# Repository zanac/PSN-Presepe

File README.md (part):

# PSN-Presepe

## Demo online Wokwi

▶️ [Apri la simulazione interattiva PSN-Presepe su Wokwi](https://wokwi.com/projects/476035349322038273)

La demo permette di provare direttamente dal browser il ciclo giorno/notte, le strisce RGB, il cielo stellato, OLED e comandi senza hardware reale.

Controller basato su Arduino Mega 2560 per la gestione modulare di un presepe a 12 V.

**Italiano** | [English](README_EN.md)

## Mockup della centralina

> Mockup concettuale della disposizione della centralina. Per i collegamenti elettrici fare riferimento agli schemi vettoriali presenti nella cartella `docs/`.

## Schema elettrico

> Questo è lo **schema di riferimento aggiornato** per il cablaggio. La striscia RGB 12 V è a positivo comune: il +12 V è diretto, mentre R, G e B vengono commutati sul lato negativo dai MOSFET.

## Mappatura hardware attuale

I pin di Arduino **non alimentano direttamente i carichi a 12 V**. Ogni uscita del Mega pilota l'ingresso `PWM` del relativo canale MOSFET. I normali carichi a due fili possono utilizzare la coppia `OUT+` / `OUT-`; la striscia RGB a positivo comune viene invece collegata come indicato qui sotto.

### MOSFET #1 — Cielo RGB

| Arduino Mega | Ingresso MOSFET | Uscita MOSFET | Carico 12 V | Controllo |
|---:|---|---|---|---|
| D2 | PWM1 | OUT1- | Striscia RGB — ritorno R | PWM / dimmerabile |
| D3 | PWM2 | OUT2- | Striscia RGB — ritorno G | PWM / dimmerabile |
| D4 | PWM3 | OUT3- | Striscia RGB — ritorno B | PWM / dimmerabile |
| — | PWM4 | OUT4+ / OUT4- | **Libero** | — |

La striscia RGB è un carico **12 V a positivo comune (anodo comune)**. Il suo unico filo `+12 V` viene collegato direttamente alla distribuzione +12 V protetta/WAGO e rimane sempre alimentato. I tre canali MOSFET commutano invece i ritorni R/G/B sul lato negativo:

```text
+12 V alimentatore ──► F1 CIELO ──┬──► +12 V comune RGB
                                   └──► DC+ MOSFET #1

RGB R ─────────────────────────────────────────► OUT1-
RGB G ─────────────────────────────────────────► OUT2-
RGB B ─────────────────────────────────────────► OUT3-

Mega D2 ───────────────────────────────────────► PWM1  (Rosso)
Mega D3 ───────────────────────────────────────► PWM2  (Verde)
Mega D4 ───────────────────────────────────────► PWM3  (Blu)

0 V alimentatore ──────────────────────────────► DC- MOSFET
```

La striscia RGB **non deve essere cablata come tre carichi indipendenti a due fili**. In questa configurazione `OUT1+`, `OUT2+` e `OUT3+` non sono necessari per la striscia RGB.

### Stelle WS2811 indirizzabili

Le stelle sono ora una stringa **WS2811 12 V da 50 pixel individualmente indirizzabili**. Non passano dal MOSFET: D5 è il segnale DATA.

```text
+12 V alimentatore ──► fusibile/distribuzione ──► WS2811 +12 V
0 V alimentatore ───────────────────────────────► WS2811 GND
Arduino GND ───────────────────────────────────► stesso 0 V comune
Mega D5 ── resistenza 330–470 Ω ──────────────► WS2811 DATA / DIN
```

Con le WS2811 il **GND Arduino deve essere comune allo 0 V dell'alimentatore 12 V**, perché il segnale DATA necessita dello stesso riferimento elettrico. Il Mega continua comunque a essere alimentato a 5 V via USB: il +12 V non deve mai essere collegato ai pin 5 V o I/O di Arduino.

Il firmware può comandare ogni stella separatamente, con luminosità e colore differenti. Dei 50 pixel disponibili, a ogni ciclo vengono selezionate casualmente 20 stelle attive, che compaiono progressivamente durante il crepuscolo e si spengono durante l'alba. Il canale 4 del MOSFET #1 rimane libero.

### MOSFET #3 e #4 — RGB laterali alba/tramonto

Per rendere alba e tramonto più dinamici vengono aggiunte **due strisce RGB analogiche 12 V da 1 m**, indipendenti dalla striscia principale:

| Posizione | Effetto | Mega R/G/B | Modulo |
|---|---|---|---|
| Sinistra | Tramonto | D7 / D11 / D12 | MOSFET #3, CH1–CH3 |
| Destra | Alba | D44 / D45 / D46 | MOSFET #4, CH1–CH3 |

Ogni striscia ha un ramo +12 V protetto dedicato: **F2 ALBA** alimenta sia il +12 V comune della striscia ALBA sia il DC+ del MOSFET #4; **F3 TRAMONTO** alimenta sia il +12 V comune della striscia TRAMONTO sia il DC+ del MOSFET #3. I ritorni R/G/B vanno ai tre OUT- del relativo modulo MOSFET. Il quarto canale di ciascun modulo resta libero. **D8 è dedicato al DATA della seconda catena WS2811 CASETTE.**

Nel firmware le palette RGB sono tarate per ottenere transizioni calde e progressive. Durante il **TRAMONTO** la laterale sinistra parte tenue, raggiunge al 38% un picco arancio chiaro e poi perde gradualmente saturazione; nell'ultimo 18% usa valori R=G=B e si spegne in bianco neutro. Il CIELO parte dalla tonalità lasciata dal GIORNO (210/82/18), diventa progressivamente bianco tenue e si spegne con R=G=B esattamente al picco del TRAMONTO. Durante l'**ALBA** la laterale destra segue una curva analoga, con picco al 38% leggermente meno arancione; il CIELO resta spento fino a quel picco e da lì cresce dolcemente fino alla tonalità iniziale del GIORNO.

### Relè ON/OFF — 4 moduli, 16 uscite

Luci case, pompe, mulino e gli altri carichi che richiedono soltanto ON/OFF vengono gestiti dai **quattro moduli relè 12 V a 4 canali**. I MOSFET restano dedicati ai carichi che richiedono PWM/dimmer.

| Gruppo | Mega | Modulo / ingresso |
|---|---:|---|
| Grp_01_01–Grp_01_04 | D25–D28 | RELÈ #1 IN1–IN4 |
| Grp_02_01–Grp_02_04 | D29–D32 | RELÈ #2 IN1–IN4 |
| Grp_03_01–Grp_03_04 | D33–D36 | RELÈ #3 IN1–IN4 |
| Grp_04_01–Grp_04_04 | D37–D40 | RELÈ #4 IN1–IN4 |

Per ogni scheda: **+12 V di alimentazione del ramo relè → DC+**, **0 V comune → DC-**. Il ramo di alimentazione delle schede relè verrà protetto e dimensionato separatamente quando sarà definita la distribuzione definitiva dei carichi. I morsetti COM/NO/NC restano disponibili per i futuri carichi. Per un carico normalmente spento si useranno normalmente COM + NO; la protezione del carico comandato è distinta da quella che alimenta l'elettronica della scheda relè.

I jumper S1–S4 permettono di scegliere HIGH/LOW trigger. Il firmware gestisce già le 16 uscite nella modalità TEST; nel simulatore viene usata la logica HIGH=ON. Prima del collegamento definitivo dei moduli reali va verificata la posizione dei jumper e, se necessario, impostato `RELE_ACTIVE_LOW` nel firmware.

#### Schedulazione scenografica dei relè

Le accensioni e gli spegnimenti durante il ciclo sono definiti nel firmware dalla tabella `SCHEDULAZIONE_RELE[]`. Ogni evento contiene:

`{ NOME_FASE, NOME_RELE, ACCESO_SPENTO, PERCENTUALE_FASE }`

La percentuale è **relativa alla singola fase**, non all'intero ciclo. Per esempio:

```cpp
const EventoRele SCHEDULAZIONE_RELE[] = {
  { TRAMONTO, Grp_01_03, true,  30 },
  { NOTTE,    Grp_01_03, false, 50 }
};
```

Con questa configurazione `Grp_01_03` si accende al **30% della fase TRAMONTO**, resta acceso durante il resto del tramonto, il crepuscolo e la prima metà della notte, quindi si spegne al **50% della fase NOTTE**.

Lo stato dei relè viene ricostruito dalla posizione corrente del ciclo, quindi rimane coerente anche usando **AVANTI**, pausa/ripresa o modificando la durata con il potenziometro. All'inizio di un nuovo ciclo, prima che siano raggiunti nuovi eventi, i relè partono spenti. In futuro la scenografia ON/OFF può essere modificata semplicemente aggiungendo o cambiando le righe della tabella.

### Display OLED ELEGOO EL-SM-008

Display di stato OLED **0,96 pollici, 128×64, I²C**, alimentazione 3,3–5 V, indirizzo I²C a 7 bit **0x3C**.

| OLED | Arduino Mega 2560 |
|---|---|
| GND | GND |
| VCC | 5 V |
| SDA | D20 / SDA |
| SCL | D21 / SCL |

Il display è **opzionale**: il firmware deve continuare a funzionare normalmente anche se l'OLED non è collegato. All'avvio il software verifica la presenza del display all'indirizzo 0x3C; se non risponde, prosegue senza OLED.

Il firmware usa il display come interfaccia di stato:
- schermata normale: **fase corrente**, percentuale di avanzamento della singola fase, barra grafica, RUN/PAUSA e durata totale del ciclo;
- START/STOP: mette in pausa o riprende il ciclo; in **PAUSA** l'OLED mostra stabilmente fase, percentuale della fase e i valori RGB correnti delle tre strisce; alla ripresa mostra brevemente **RIPRESA**;
- AVANTI: popup **AVANTI** con la nuova fase;
- TEST: feedback **TEST**;
- variazione significativa del B10K: popup **VELOCITA** con la durata effettiva del ciclo in minuti.

I popup durano circa 1,8 secondi e poi il display torna automaticamente alla schermata della fase. L'aggiornamento normale dell'OLED è non bloccante; l'assenza del display non impedisce l'avvio del controllore.

> Nota: sul Mega 2560 l'I²C hardware usa **D20=SDA** e **D21=SCL**. Eventuali esempi che indicano D21/D22 si riferiscono ad altre piattaforme, ad esempio ESP32.

Quando il ciclo viene messo in **PAUSA**, l'OLED mostra stabilmente la fase e la percentuale raggiunta, insieme ai valori RGB correnti delle tre strisce:

- `C R,G,B` = cielo RGB principale;
- `T R,G,B` = RGB laterale TRAMONTO;
- `A R,G,B` = RGB laterale ALBA.

I valori sono quelli logici 0–255 inviati al PWM e permettono di fermare la scena su una tonalità interessante, trascriverla e riutilizzarla successivamente per la taratura dei colori.

### Comandi

| Arduino Mega | Dispositivo | Collegamento |
|---:|---|---|
| D22 | Pulsante START/STOP | D22 ↔ pulsante ↔ GND logica |
| D23 | Pulsante AVANTI | D23 ↔ pulsante ↔ GND logica |
| D24 | Pulsante TEST | D24 ↔ pulsante ↔ GND logica |
| A0 | Potenziometro B10K velocità ciclo | 5 V ↔ esterno, A0 ↔ cursore, GND ↔ esterno |

> **Prova senza potenziometro:** se il potenziometro B10K su A0 viene scollegato, non lasciare A0 flottante: la lettura analogica potrebbe assumere valori casuali e far variare la durata del ciclo. Per una prova stabile, collegare temporaneamente **A0 direttamente a GND**. Il firmware leggerà A0=0, corrispondente alla durata minima del ciclo di **1 minuto**.

I pulsanti utilizzano `INPUT_PULLUP`, quindi non richiedono una resistenza di pull-up esterna. Il GND logico di Arduino viene distribuito tramite WAGO agli ingressi `GND1...GND4` dei MOSFET e ai comandi.

## Sequenza di inizializzazione all'accensione

Prima di iniziare il normale ciclo scenografico, il firmware esegue un **autotest visivo di circa 21,625 secondi**, seguito dalla schermata **PRONTO** per 900 ms. I relè restano spenti e le uscite luminose vengono provate in sequenza:

1. **ALBA** — striscia RGB alba in bianco brillante per circa **4,325 s**;
2. **CIELO** — striscia RGB principale in bianco brillante per circa **4,325 s**;
3. **TRAMONTO** — striscia RGB tramonto in bianco brillante per circa **4,325 s**;
4. **STELLE** — tutti i 50 pixel WS2811 in bianco brillante per circa **4,325 s**;
5. **CASETTE** — seconda catena WS2811 su D8 in bianco brillante per circa **4,325 s**.

La melodia **Astro del ciel** è stata dilatata a circa **21,625 s** per mantenere sincronizzati i cinque passi dell'autotest, la progress bar OLED e la musica. Al termine tutte le uscite vengono spente, compare **PRONTO** per 900 ms e solo dopo viene azzerato il timer del ciclo: il tempo di boot **non fa parte** del ciclo scenografico.

Durante l'intera sequenza l'OLED mostra **Inizializzazione**, il nome dell'uscita in prova, la percentuale complessiva e una progress bar.

## Funzionamento scenografico

Il ciclo automatico usa tre velocità discrete selezionate dal potenziometro: **1, 3 o 5 minuti**. Le fasi non hanno una durata fissa in secondi: occupano una percentuale precisa del ciclo, quindi tutti i tempi scalano linearmente quando si cambia la durata totale.

| Fase | Posizione nel ciclo | Quota ciclo | Ciclo 1 min | Ciclo 3 min | Ciclo 5 min |
|---|---:|---:|---:|---:|---:|
| **GIORNO** | 0–40% | 40% | 24 s | 72 s | 120 s |
| **TRAMONTO** | 40–50% | 10% | 6 s | 18 s | 30 s |
| **CREPUSCOLO** | 50–55% | 5% | 3 s | 9 s | 15 s |
| **NOTTE** | 55–85% | 30% | 18 s | 54 s | 90 s |
| **ALBA** | 85–100% | 15% | 9 s | 27 s | 45 s |

Questa tabella è il riferimento temporale del firmware. Per una durata intermedia, il tempo di ogni fase è semplicemente la percentuale indicata della durata totale.

1. **GIORNO (0–40%)** — stelle e laterali spente. Il CIELO parte caldo (210/82/18), raggiunge progressivamente il bianco pieno al 33% della fase, torna alla tonalità calda entro il 66% e la mantiene fino al TRAMONTO.
2. **TRAMONTO (40–50%)** — la laterale sinistra parte tenue e raggiunge al **38% della fase** un picco arancio chiaro (155/92/16), poi cala perdendo saturazione; nell'ultimo **18%** R=G=B e i tre canali si spengono insieme. Il CIELO parte dalla tonalità finale del GIORNO, si attenua verso un bianco tenue e raggiunge 0/0/0 esattamente al **38%**, cioè al picco della laterale, restando poi spento. Le stelle restano spente.
3. **CREPUSCOLO (50–55%)** — CIELO e laterali sono spenti. Viene generata una nuova disposizione casuale e compaiono progressivamente, una alla volta, **20 stelle scelte tra i 50 pixel disponibili**.
4. **NOTTE (55–85%)** — CIELO e laterali restano completamente spenti. Le 20 stelle rimangono attive con luminosità massime differenti e cicli asincroni individuali di variazione. Il ciclo individuale di ciascuna stella dura circa **6,4–12,2 s**, senza modificare la durata della fase NOTTE.
5. **ALBA (85–100%)** — le stelle iniziano a dissolversi fin dall'inizio. La laterale destra parte con pochissima luce chiara, raggiunge al **38% della fase** un picco arancio chiaro (155/78/22), poi cala perdendo saturazione; nell'ultimo **18%** R=G=B e si spegne in modo simultaneo. Il CIELO resta completamente spento fino al picco dell'ALBA; dal **38%** parte a luminosità molto bassa (10/4/1) e cresce dolcemente fino a 210/82/18, esattamente la tonalità con cui inizia il nuovo GIORNO.

La seconda catena WS2811 **CASETTE su D8** viene inizializzata dal firmware e verificata durante boot e TEST manuale, ma nel normale ciclo scenografico viene mantenuta spenta finché non saranno definite le sue accensioni.

A ogni nuovo CREPUSCOLO viene generata una nuova selezione delle stelle e delle relative luminosità. Il colore delle stelle è **bianco caldo**.

## Manuale di montaggio filo per filo

Questa sezione è il riferimento pratico per il cablaggio. **Non lavorare mai sul circuito con l'alimentatore 230 V collegato.** **Il +12 V non deve mai essere collegato direttamente a un pin del Mega, a 5 V, A0, SDA/SCL o DATA:** il Mega lavora a logica 5 V e i pin I/O non sono ingressi a 12 V. Il Mega è alimentato separatamente via USB 5 V. Il +12 V alimenta soltanto carichi e moduli di potenza. Lo **0 V 12 V e GND Arduino devono essere in comune** per i segnali PWM e per DATA WS2811.

### 1. Distribuzione alimentazione 12 V

> **Cosa significa “+12 V protetto” in questo manuale?**  
> Significa semplicemente che il filo **positivo +12 V è passato attraverso un fusibile prima di raggiungere il carico**. Il fusibile va quindi inserito **sul polo positivo (+12 V)** del ramo da proteggere, non sullo 0 V/negativo.
>
> Esempio: `alimentatore +12 V → fusibile → striscia LED +12 V`.
>
> Se un cavo o un utilizzatore va in cortocircuito, il fusibile di quel ramo interrompe il positivo e protegge soprattutto **cablaggio e connettori** dalla forte corrente che l'alimentatore potrebbe fornire. Quando nelle tabelle seguenti compare la dicitura **“+12 V protetto”**, bisogna quindi leggere: **“+12 V proveniente da un'uscita del portafusibili”**.

Portare il **+12 V** dell'alimentatore all'ingresso positivo del portafusibili/distributore. Ogni uscita del portafusibili avrà il proprio fusibile e alimenterà un singolo ramo: RGB principale, stelle WS2811, RGB tramonto, RGB alba e gli altri carichi. Lo **0 V (negativo)** non passa attraverso questi fusibili di ramo: viene portato alla barra negativa del distributore, se presente, oppure a una morsettiera/WAGO 0 V comune.

```text
ALIMENTATORE 12 V

 +12 V ──► ingresso + portafusibili
                │
                ├─► F1 CIELO ─────► +12 V RGB principale + DC+ MOSFET #1
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
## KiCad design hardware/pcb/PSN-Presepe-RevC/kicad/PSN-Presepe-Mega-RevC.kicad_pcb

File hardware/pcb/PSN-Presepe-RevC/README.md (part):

# PSN-Presepe PCB — Rev C (manufacturing package)

Rev C supersedes Rev B. It fixes the Rev B blocking defects, and every step of the
build is checked by KiCad DRC plus two independent checkers (one on the board file,
one on the Gerber/Excellon files the fab will actually use).

**Status: official Rev C source and manufacturing candidate.** The accepted design target is 6 mm MAINS-to-SELV, 5 mm between different relay contact circuits, and 2 mm within the same relay contact circuit. Final ordering remains gated by KiCad 10 CI plus the pre-order checklist below. That checklist
is a 1:1 paper fit test and confirming the exact part numbers.

## 1. What changed from Rev B

| # | Rev B defect | Rev C fix |
|---|---|---|
| 1 | **Omron G5Q-1 footprint was mirrored** (pads 4/5 on the wrong side). The relays could not be inserted. | Official KiCad footprint `Relay_THT:Relay_SPDT_Omron-G5Q-1` (top view). Verified against the KiCad library hole pattern. |
| 2 | **NO/NC swapped**: relay pad 3 was wired as NC and pad 4 as NO. The terminal marked "NO" was really NC. | G5Q-1 pad 3 = **NO**, pad 4 = **NC** (per the KiCad `Relay` symbol lib G5Q-1 and the G5Q-1A, which is the NO-only version that keeps pin 3). Terminals are still 1 = COM, 2 = NO, 3 = NC. |
| 3 | **ULN2803 footprint had 10.16 mm (400 mil) rows.** The DIP-18 package could not be inserted. | Standard `Package_DIP:DIP-18_W7.62mm` (300 mil). |
| 4 | **Relay isolation rule never ran.** The rules used `=~` regular expressions, which KiCad custom rules do not support, so they matched nothing. The CI also only counted the rule lines in the file. Measured contact copper was down to 0.20 mm from other relays, +12 V and logic. | New wildcard-based rules: **6 mm** between relay contacts and everything else, **5 mm** between different relays, **2 mm** between COM/NO/NC of the same relay, **3 mm** to the board edge, **6 mm** to non-MAINS holes. A positive control shows each rule is active: forcing each rule to an impossible value makes the DRC flag it (`reports/positive-control-summary.txt`). |
| 5 | **Relay contact traces up to 185 mm long**, bundled across the board between other circuits. | Relay section re-placed so **each relay sits directly behind its own terminal block**. Contact paths are 10–25 mm long, drawn on **both layers at 2 mm**, with no vias. |
| 6 | Buzzer driven directly from D6. A 16–42 Ω magnetic buzzer would overload the pin and the Mega 5 V regulator. | `RBZ1` 220 Ω added in series (net `BUZZER_DRV`). Safe with a piezo or a magnetic buzzer. |
| 7 | MOSFET block courtyards overlapped: resistor leads sat under the TO-220 bodies. | MOSFET block re-laid out as 3×3 cells (RG + RPD to the left of each TO-220). No courtyard overlaps. |
| 8 | Rev B `.kicad_sch`: every global label sat at the **vertically mirrored** pin position (library Y axis points up). The schematic netlist did not match the PCB (for example J1 +12V on pin 2). | Schematic regenerated from the PCB. A KiCad-exported netlist matches the PCB pin-for-pin: 315/315 pins, 0 mismatches. |

Unchanged:
- All 119 Rev B nets and the firmware pin map (D2–D8, D11/D12, D20–D46, A0, VIN). This is checked by parsing `PSN-Presepe.ino`.
- Board outline 300 × 180 mm, 2 layers.
- Low-voltage terminal positions.
- The Mega 2560 shield footprint and the MOSFET circuit.

## 2. Electrical design summary

| Net class | Width | Clearance | Notes |
|---|---|---|---|
| MAINS (R*_COM/NO/NC) | 2.0 mm on F.Cu **and** B.Cu | 6 mm to SELV, 5 mm between relays, 2 mm within a relay | No vias. Locked tracks. |
| POWER (+12V, GND) | **3 mm trunks**, 1 mm branches | 0.3 mm | Trunks: J1 to the strip terminals (CIELO/TRAMONTO/ALBA/STELLE/CASETTE), and the MOSFET sources back to J1, with 1.5 mm stubs into the TO-220 pins. Branches carry < 0.6 A: relay coils, ULN COM, Mega VIN, caps. |
| RGB (*_NEG) | 1.5 mm | 0.3 mm | MOSFET drain to the strip terminal, about 1.7 A per channel. |
| P5V (+5V_MEGA) | 0.8 mm | 0.25 mm | |
| COIL | 0.4 mm | 0.2 mm | 33 mA per coil. |
| Signals | 0.25 mm | 0.2 mm | |

Current capacity (IPC-2221, external layer, 10 °C rise, 1 oz):
- 3 mm trunk: about 5.3 A.
- 1.5 mm RGB: about 3.2 A.
- Relay contact (2 × 2 mm, both layers): about 7.9 A.

With **2 oz copper (recommended)** these roughly double. This gives margin over the 5.5 A board budget and lets the relay channels use more of their 10 A rating. The IRLZ44N dissipates about 0.1 W at 1.7 A, so no heatsink is needed.

The isolation distances are a conservative design target for 230 V AC, pollution degree 2, FR-4. They are **not a safety certification**. Use a closed enclosure, put fuses on the mains feed, use wire rated for the load, and keep mains wiring away from the low-voltage side.

## 3. Verification (all in `reports/`)

| Check | Tool | Result |
|---|---|---|
| DRC with project rules + `.kicad_dru` | KiCad 7.0.11 pcbnew | **0 violations, 0 unconnected** |
| Each isolation rule actually active | KiCad DRC, one rule forced impossible per run | selv / inter / intra / edge all fire |
| Board geometry: shorts, clearances by class, connectivity, holes, edge, widths, pinout, footprint patterns, netlist parity with Rev B + listed changes, firmware pins, Mega keep-out | `build/verify.py` (shapely, no KiCad) | **ALL CHECKS PASSED** |
| Manufacturing files: Gerber copper islands vs X2 net attributes, clearances incl. MAINS, annular rings, NPTH, mask openings, tented vias, outline | `build/verify_gerbers.py` (gerbonara, no KiCad) | **ALL GERBER CHECKS PASSED** |
| Schematic ↔ PCB | `kicad-cli sch export netlist` + `check_sch_parity.py` | 315/315 pins match |

Project decision (2026-10-04): the 5 mm inter-relay target is accepted for Rev C; the measured 5.23 mm is therefore compliant and is not a waiver. The 6 mm target remains mandatory between relay-contact copper and SELV.

Measured minimum distances:

| Pair | Measured | Required |
|---|---|---|
| MAINS ↔ SELV | 6.30 mm | 6 |
| MAINS between relays | 5.23 mm | 5 |
| MAINS within a relay | 2.15 mm | 2 |
| MAINS ↔ mounting holes | 11.7 mm | — |

Not done here:
- **ERC**, because `kicad-cli` 7 has no `sch erc`. Run it in KiCad 8/9/10. The schematic is pure net labels, so the only expected messages are annotation notes about the `J_*` references, which have no trailing number.
- The build used **KiCad 7.0.11**, because this environment could not download KiCad 10. KiCad 10 opens these files and converts them on save. Re-running the DRC in KiCad 10 before ordering is a good final cross-check.

## 4. Ordering (e.g. JLCPCB / PCBWay / Aisler)

Upload `manufacturing/PSN-Presepe-Mega-RevC-gerbers.zip` (Gerber X2 + Excellon PTH/NPTH, Protel extensions) with these settings:

- 2 layers, 300 × 180 mm, FR-4 1.6 mm.
- **2 oz outer copper (recommended; 1 oz acceptable).**
- HASL or ENIG finish, any mask colour, white silkscreen.
- Minimum track/space 0.25/0.2 mm. Minimum drill 0.3 mm (vias), no castellations.

The board is all through-hole, so assembly is by hand. `CPL.csv` is included only for completeness.

## 5. Pre-order checklist

1. **Print `manufacturing/PSN-Presepe-Mega-RevC-1to1-A3-top.pdf` at 100 % on A3.** Check the scale with a ruler (300 mm outline). Push a real G5Q-1, a ULN2803 (or its socket), a 3-way MKDS terminal, an IRLZ44N, the RK09K potentiometer and the buzzer through the paper.
2. Confirm the exact order codes:
   - G5Q-1 **DC12** suffix (the standard G5Q-1 has the 10 A contact).
   - The terminal block series, with 5.08 mm pitch and wire entry towards the board edge.
   - The buzzer pitch (7.6 mm).
3. Wire entry: all terminals face outward (top row up, right column right, bottom row down). This was verified against the KiCad 3D model of the MKDS 1,5 horizontal terminal.
4. Put a strip of Kapton tape on the Mega USB-B shell. There are no vias above it, but the bottom-side tracks are only covered by solder mask.

## 6. Firmware notes (no change required)

- Relay outputs are unchanged (D25–D40, active HIGH through the ULN2803).
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
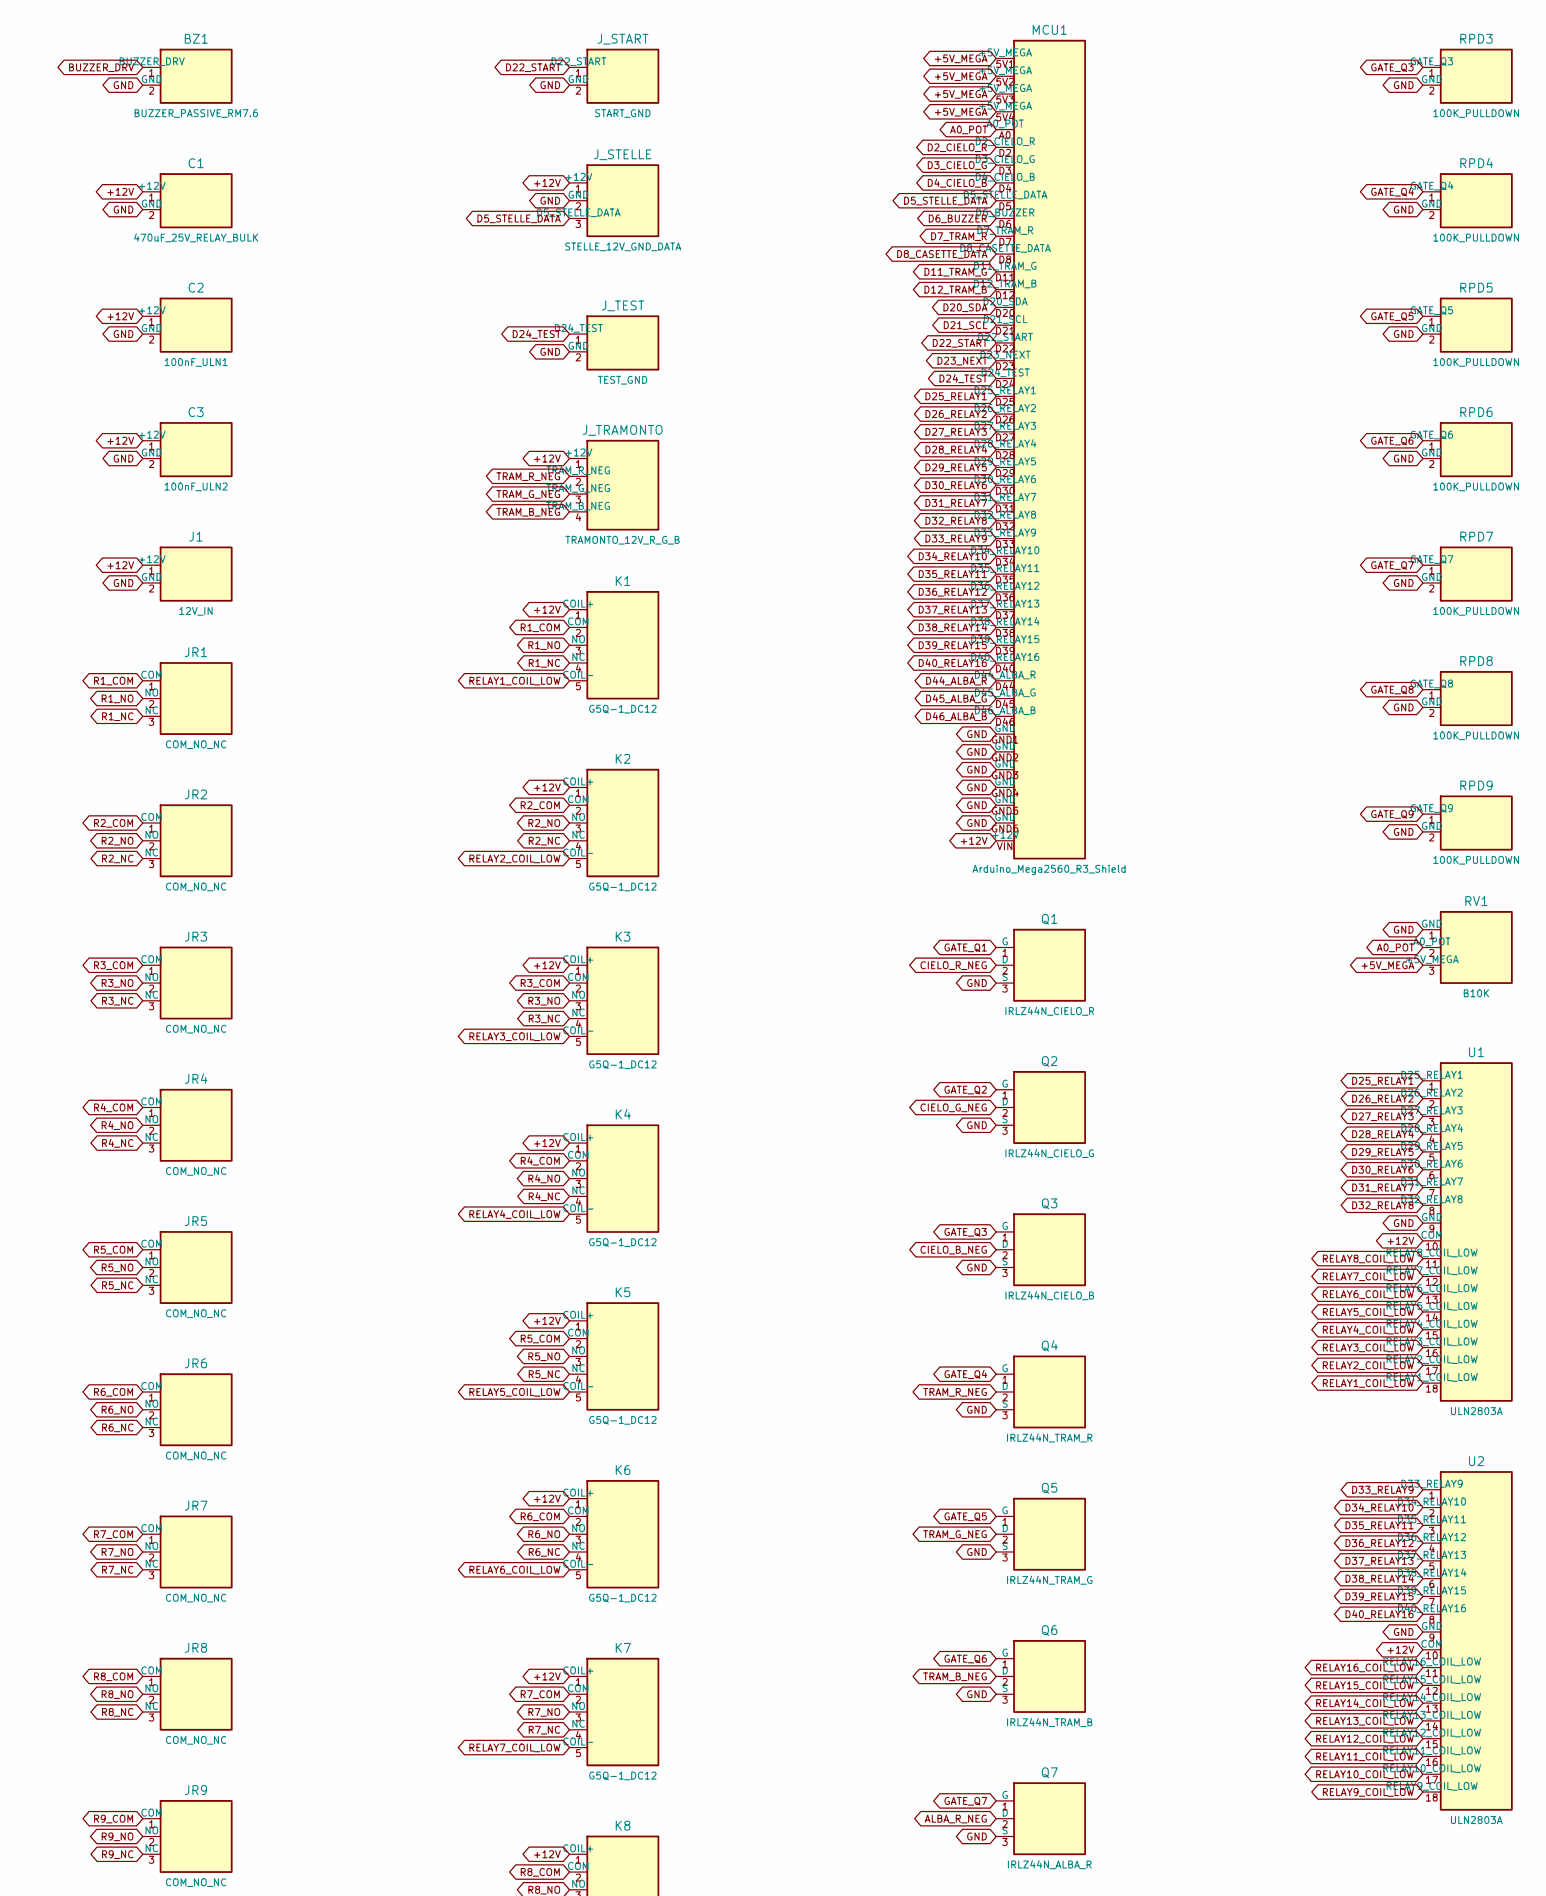
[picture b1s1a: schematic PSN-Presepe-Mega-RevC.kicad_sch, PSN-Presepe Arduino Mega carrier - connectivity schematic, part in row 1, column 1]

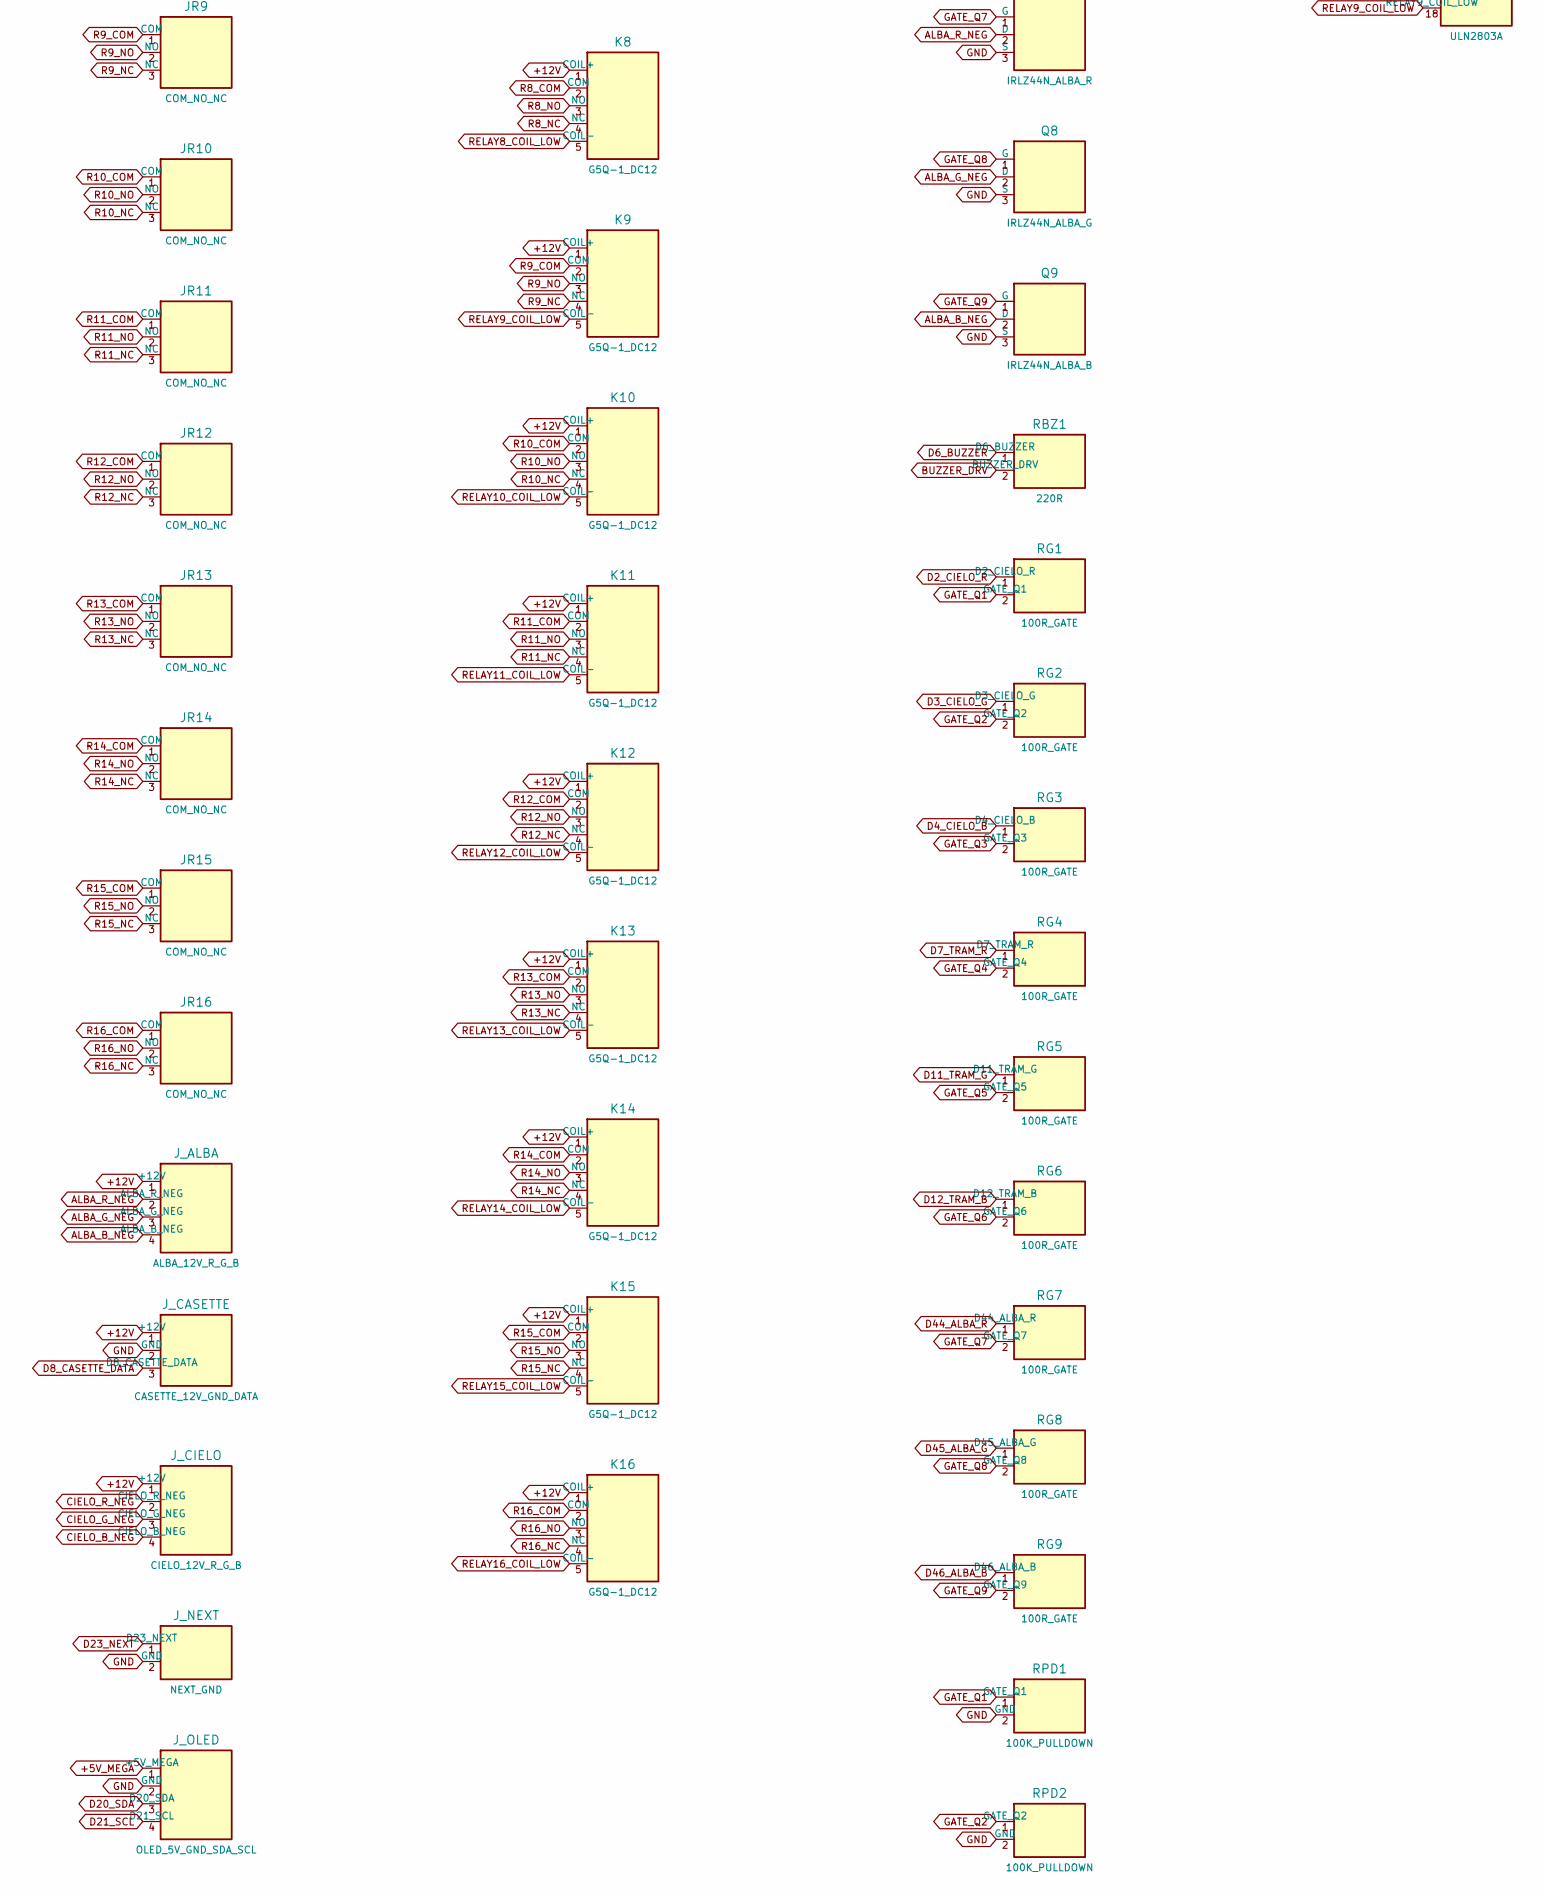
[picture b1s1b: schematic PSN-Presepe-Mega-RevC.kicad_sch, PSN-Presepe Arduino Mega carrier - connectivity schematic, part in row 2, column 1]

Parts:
BZ1: BUZZER_PASSIVE_RM7.6; Buzzer_12x9.5RM7.6
C1: 470uF_25V_RELAY_BULK; C_Radial_D10.0mm_H12.5mm_P5.00mm
C2: 100nF_ULN1; C_Disc_D5.0mm_W2.5mm_P5.00mm
C3: 100nF_ULN2; C_Disc_D5.0mm_W2.5mm_P5.00mm
J1: 12V_IN; TerminalBlock_Phoenix_MKDS-1,5-2-5.08_1x02_P5.08mm_Horizont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
JR1, JR2, JR3, JR4, JR5, JR6, JR7, JR8, JR9, JR10, JR11, JR12, JR13, JR14, JR15, JR16: COM_NO_NC; TerminalBlock_Phoenix_MKDS-1,5-3-5.08_1x03_P5.08mm_Horizont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
J_ALBA: ALBA_12V_R_G_B; TerminalBlock_Phoenix_MKDS-1,5-4-5.08_1x04_P5.08mm_Horizont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
J_CASETTE: CASETTE_12V_GND_DATA; TerminalBlock_Phoenix_MKDS-1,5-3-5.08_1x03_P5.08mm_Horizont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
J_CIELO: CIELO_12V_R_G_B; TerminalBlock_Phoenix_MKDS-1,5-4-5.08_1x04_P5.08mm_Horizont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
J_NEXT: NEXT_GND; TerminalBlock_Phoenix_MKDS-1,5-2-5.08_1x02_P5.08mm_Horizont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
J_OLED: OLED_5V_GND_SDA_SCL; TerminalBlock_Phoenix_MKDS-1,5-4-5.08_1x04_P5.08mm_Horizont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
J_START: START_GND; TerminalBlock_Phoenix_MKDS-1,5-2-5.08_1x02_P5.08mm_Horizont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
J_STELLE: STELLE_12V_GND_DATA; TerminalBlock_Phoenix_MKDS-1,5-3-5.08_1x03_P5.08mm_Horizont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
J_TEST: TEST_GND; TerminalBlock_Phoenix_MKDS-1,5-2-5.08_1x02_P5.08mm_Horizont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
J_TRAMONTO: TRAMONTO_12V_R_G_B; TerminalBlock_Phoenix_MKDS-1,5-4-5.08_1x04_P5.08mm_Horizont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
K1, K2, K3, K4, K5, K6, K7, K8, K9, K10, K11, K12, K13, K14, K15, K16: G5Q-1_DC12; Relay_SPDT_Omron-G5Q-1
MCU1: Arduino_Mega2560_R3_Shield
Q1: IRLZ44N_CIELO_R; TO-220-3_Vertical
Q2: IRLZ44N_CIELO_G; TO-220-3_Vertical
Q3: IRLZ44N_CIELO_B; TO-220-3_Vertical
Q4: IRLZ44N_TRAM_R; TO-220-3_Vertical
Q5: IRLZ44N_TRAM_G; TO-220-3_Vertical
Q6: IRLZ44N_TRAM_B; TO-220-3_Vertical
Q7: IRLZ44N_ALBA_R; TO-220-3_Vertical
Q8: IRLZ44N_ALBA_G; TO-220-3_Vertical
Q9: IRLZ44N_ALBA_B; TO-220-3_Vertical
RBZ1: 220R; R_Axial_DIN0207_L6.3mm_D2.5mm_P10.16mm_Horizontal
RG1, RG2, RG3, RG4, RG5, RG6, RG7, RG8, RG9: 100R_GATE; R_Axial_DIN0207_L6.3mm_D2.5mm_P10.16mm_Horizontal
RPD1, RPD2, RPD3, RPD4, RPD5, RPD6, RPD7, RPD8, RPD9: 100K_PULLDOWN; R_Axial_DIN0207_L6.3mm_D2.5mm_P10.16mm_Horizontal
RV1: B10K; Potentiometer_Alps_RK09K_Single_Horizontal
U1, U2: ULN2803A; DIP-18_W7.62mm

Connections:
+5V_MEGA: J_OLED.1 (+5V_MEGA), MCU1.5V1 (+5V_MEGA), MCU1.5V2 (+5V_MEGA), MCU1.5V3 (+5V_MEGA), MCU1.5V4 (+5V_MEGA), RV1.3 (+5V_MEGA)
+12V: C1.1 (+12V), C2.1 (+12V), C3.1 (+12V), J1.1 (+12V), J_ALBA.1 (+12V), J_CASETTE.1 (+12V), J_CIELO.1 (+12V), J_STELLE.1 (+12V), J_TRAMONTO.1 (+12V), K1.1 (COIL+), K2.1 (COIL+), K3.1 (COIL+), K4.1 (COIL+), K5.1 (COIL+), K6.1 (COIL+), K7.1 (COIL+), K8.1 (COIL+), K9.1 (COIL+), K10.1 (COIL+), K11.1 (COIL+), K12.1 (COIL+), K13.1 (COIL+), K14.1 (COIL+), K15.1 (COIL+), K16.1 (COIL+), MCU1.VIN (+12V), U1.10 (COM), U2.10 (COM)
A0_POT: MCU1.A0 (A0_POT), RV1.2 (A0_POT)
ALBA_B_NEG: J_ALBA.4 (ALBA_B_NEG), Q9.2 (D)
ALBA_G_NEG: J_ALBA.3 (ALBA_G_NEG), Q8.2 (D)
ALBA_R_NEG: J_ALBA.2 (ALBA_R_NEG), Q7.2 (D)
BUZZER_DRV: BZ1.1 (BUZZER_DRV), RBZ1.2 (BUZZER_DRV)
CIELO_B_NEG: J_CIELO.4 (CIELO_B_NEG), Q3.2 (D)
CIELO_G_NEG: J_CIELO.3 (CIELO_G_NEG), Q2.2 (D)
CIELO_R_NEG: J_CIELO.2 (CIELO_R_NEG), Q1.2 (D)
D2_CIELO_R: MCU1.D2 (D2_CIELO_R), RG1.1 (D2_CIELO_R)
D3_CIELO_G: MCU1.D3 (D3_CIELO_G), RG2.1 (D3_CIELO_G)
D4_CIELO_B: MCU1.D4 (D4_CIELO_B), RG3.1 (D4_CIELO_B)
D5_STELLE_DATA: J_STELLE.3 (D5_STELLE_DATA), MCU1.D5 (D5_STELLE_DATA)
D6_BUZZER: MCU1.D6 (D6_BUZZER), RBZ1.1 (D6_BUZZER)
D7_TRAM_R: MCU1.D7 (D7_TRAM_R), RG4.1 (D7_TRAM_R)
D8_CASETTE_DATA: J_CASETTE.3 (D8_CASETTE_DATA), MCU1.D8 (D8_CASETTE_DATA)
D11_TRAM_G: MCU1.D11 (D11_TRAM_G), RG5.1 (D11_TRAM_G)
D12_TRAM_B: MCU1.D12 (D12_TRAM_B), RG6.1 (D12_TRAM_B)
D20_SDA: J_OLED.3 (D20_SDA), MCU1.D20 (D20_SDA)
D21_SCL: J_OLED.4 (D21_SCL), MCU1.D21 (D21_SCL)
D22_START: J_START.1 (D22_START), MCU1.D22 (D22_START)
D23_NEXT: J_NEXT.1 (D23_NEXT), MCU1.D23 (D23_NEXT)
D24_TEST: J_TEST.1 (D24_TEST), MCU1.D24 (D24_TEST)
D25_RELAY1: MCU1.D25 (D25_RELAY1), U1.1 (D25_RELAY1)
D26_RELAY2: MCU1.D26 (D26_RELAY2), U1.2 (D26_RELAY2)
D27_RELAY3: MCU1.D27 (D27_RELAY3), U1.3 (D27_RELAY3)
D28_RELAY4: MCU1.D28 (D28_RELAY4), U1.4 (D28_RELAY4)
D29_RELAY5: MCU1.D29 (D29_RELAY5), U1.5 (D29_RELAY5)
D30_RELAY6: MCU1.D30 (D30_RELAY6), U1.6 (D30_RELAY6)
D31_RELAY7: MCU1.D31 (D31_RELAY7), U1.7 (D31_RELAY7)
D32_RELAY8: MCU1.D32 (D32_RELAY8), U1.8 (D32_RELAY8)
D33_RELAY9: MCU1.D33 (D33_RELAY9), U2.1 (D33_RELAY9)
D34_RELAY10: MCU1.D34 (D34_RELAY10), U2.2 (D34_RELAY10)
D35_RELAY11: MCU1.D35 (D35_RELAY11), U2.3 (D35_RELAY11)
D36_RELAY12: MCU1.D36 (D36_RELAY12), U2.4 (D36_RELAY12)
D37_RELAY13: MCU1.D37 (D37_RELAY13), U2.5 (D37_RELAY13)
D38_RELAY14: MCU1.D38 (D38_RELAY14), U2.6 (D38_RELAY14)
D39_RELAY15: MCU1.D39 (D39_RELAY15), U2.7 (D39_RELAY15)
D40_RELAY16: MCU1.D40 (D40_RELAY16), U2.8 (D40_RELAY16)
D44_ALBA_R: MCU1.D44 (D44_ALBA_R), RG7.1 (D44_ALBA_R)
D45_ALBA_G: MCU1.D45 (D45_ALBA_G), RG8.1 (D45_ALBA_G)
D46_ALBA_B: MCU1.D46 (D46_ALBA_B), RG9.1 (D46_ALBA_B)
GATE_Q1: Q1.1 (G), RG1.2 (GATE_Q1), RPD1.1 (GATE_Q1)
GATE_Q2: Q2.1 (G), RG2.2 (GATE_Q2), RPD2.1 (GATE_Q2)
GATE_Q3: Q3.1 (G), RG3.2 (GATE_Q3), RPD3.1 (GATE_Q3)
GATE_Q4: Q4.1 (G), RG4.2 (GATE_Q4), RPD4.1 (GATE_Q4)
GATE_Q5: Q5.1 (G), RG5.2 (GATE_Q5), RPD5.1 (GATE_Q5)
GATE_Q6: Q6.1 (G), RG6.2 (GATE_Q6), RPD6.1 (GATE_Q6)
GATE_Q7: Q7.1 (G), RG7.2 (GATE_Q7), RPD7.1 (GATE_Q7)
GATE_Q8: Q8.1 (G), RG8.2 (GATE_Q8), RPD8.1 (GATE_Q8)
GATE_Q9: Q9.1 (G), RG9.2 (GATE_Q9), RPD9.1 (GATE_Q9)
GND: BZ1.2 (GND), C1.2 (GND), C2.2 (GND), C3.2 (GND), J1.2 (GND), J_CASETTE.2 (GND), J_NEXT.2 (GND), J_OLED.2 (GND), J_START.2 (GND), J_STELLE.2 (GND), J_TEST.2 (GND), MCU1.GND1 (GND), MCU1.GND2 (GND), MCU1.GND3 (GND), MCU1.GND4 (GND), MCU1.GND5 (GND), MCU1.GND6 (GND), Q1.3 (S), Q2.3 (S), Q3.3 (S), Q4.3 (S), Q5.3 (S), Q6.3 (S), Q7.3 (S), Q8.3 (S), Q9.3 (S), RPD1.2 (GND), RPD2.2 (GND), RPD3.2 (GND), RPD4.2 (GND), RPD5.2 (GND), RPD6.2 (GND), RPD7.2 (GND), RPD8.2 (GND), RPD9.2 (GND), RV1.1 (GND), U1.9 (GND), U2.9 (GND)
R1_COM: JR1.1 (COM), K1.2 (COM)
R1_NC: JR1.3 (NC), K1.4 (NC)
R1_NO: JR1.2 (NO), K1.3 (NO)
R2_COM: JR2.1 (COM), K2.2 (COM)
R2_NC: JR2.3 (NC), K2.4 (NC)
R2_NO: JR2.2 (NO), K2.3 (NO)
R3_COM: JR3.1 (COM), K3.2 (COM)
R3_NC: JR3.3 (NC), K3.4 (NC)
R3_NO: JR3.2 (NO), K3.3 (NO)
R4_COM: JR4.1 (COM), K4.2 (COM)
R4_NC: JR4.3 (NC), K4.4 (NC)
R4_NO: JR4.2 (NO), K4.3 (NO)
R5_COM: JR5.1 (COM), K5.2 (COM)
R5_NC: JR5.3 (NC), K5.4 (NC)
R5_NO: JR5.2 (NO), K5.3 (NO)
R6_COM: JR6.1 (COM), K6.2 (COM)
R6_NC: JR6.3 (NC), K6.4 (NC)
R6_NO: JR6.2 (NO), K6.3 (NO)
R7_COM: JR7.1 (COM), K7.2 (COM)
R7_NC: JR7.3 (NC), K7.4 (NC)
R7_NO: JR7.2 (NO), K7.3 (NO)
R8_COM: JR8.1 (COM), K8.2 (COM)
R8_NC: JR8.3 (NC), K8.4 (NC)
R8_NO: JR8.2 (NO), K8.3 (NO)
R9_COM: JR9.1 (COM), K9.2 (COM)
R9_NC: JR9.3 (NC), K9.4 (NC)
R9_NO: JR9.2 (NO), K9.3 (NO)
R10_COM: JR10.1 (COM), K10.2 (COM)
R10_NC: JR10.3 (NC), K10.4 (NC)
R10_NO: JR10.2 (NO), K10.3 (NO)
R11_COM: JR11.1 (COM), K11.2 (COM)
R11_NC: JR11.3 (NC), K11.4 (NC)
R11_NO: JR11.2 (NO), K11.3 (NO)
R12_COM: JR12.1 (COM), K12.2 (COM)
R12_NC: JR12.3 (NC), K12.4 (NC)
R12_NO: JR12.2 (NO), K12.3 (NO)
R13_COM: JR13.1 (COM), K13.2 (COM)
R13_NC: JR13.3 (NC), K13.4 (NC)
R13_NO: JR13.2 (NO), K13.3 (NO)
R14_COM: JR14.1 (COM), K14.2 (COM)
R14_NC: JR14.3 (NC), K14.4 (NC)
R14_NO: JR14.2 (NO), K14.3 (NO)
R15_COM: JR15.1 (COM), K15.2 (COM)
R15_NC: JR15.3 (NC), K15.4 (NC)
R15_NO: JR15.2 (NO), K15.3 (NO)
R16_COM: JR16.1 (COM), K16.2 (COM)
R16_NC: JR16.3 (NC), K16.4 (NC)
R16_NO: JR16.2 (NO), K16.3 (NO)
RELAY1_COIL_LOW: K1.5 (COIL-), U1.18 (RELAY1_COIL_LOW)
RELAY2_COIL_LOW: K2.5 (COIL-), U1.17 (RELAY2_COIL_LOW)
RELAY3_COIL_LOW: K3.5 (COIL-), U1.16 (RELAY3_COIL_LOW)
RELAY4_COIL_LOW: K4.5 (COIL-), U1.15 (RELAY4_COIL_LOW)
RELAY5_COIL_LOW: K5.5 (COIL-), U1.14 (RELAY5_COIL_LOW)
RELAY6_COIL_LOW: K6.5 (COIL-), U1.13 (RELAY6_COIL_LOW)
RELAY7_COIL_LOW: K7.5 (COIL-), U1.12 (RELAY7_COIL_LOW)
RELAY8_COIL_LOW: K8.5 (COIL-), U1.11 (RELAY8_COIL_LOW)
RELAY9_COIL_LOW: K9.5 (COIL-), U2.18 (RELAY9_COIL_LOW)
RELAY10_COIL_LOW: K10.5 (COIL-), U2.17 (RELAY10_COIL_LOW)
RELAY11_COIL_LOW: K11.5 (COIL-), U2.16 (RELAY11_COIL_LOW)
RELAY12_COIL_LOW: K12.5 (COIL-), U2.15 (RELAY12_COIL_LOW)
RELAY13_COIL_LOW: K13.5 (COIL-), U2.14 (RELAY13_COIL_LOW)
RELAY14_COIL_LOW: K14.5 (COIL-), U2.13 (RELAY14_COIL_LOW)
RELAY15_COIL_LOW: K15.5 (COIL-), U2.12 (RELAY15_COIL_LOW)
RELAY16_COIL_LOW: K16.5 (COIL-), U2.11 (RELAY16_COIL_LOW)
TRAM_B_NEG: J_TRAMONTO.4 (TRAM_B_NEG), Q6.2 (D)
TRAM_G_NEG: J_TRAMONTO.3 (TRAM_G_NEG), Q5.2 (D)
TRAM_R_NEG: J_TRAMONTO.2 (TRAM_R_NEG), Q4.2 (D)

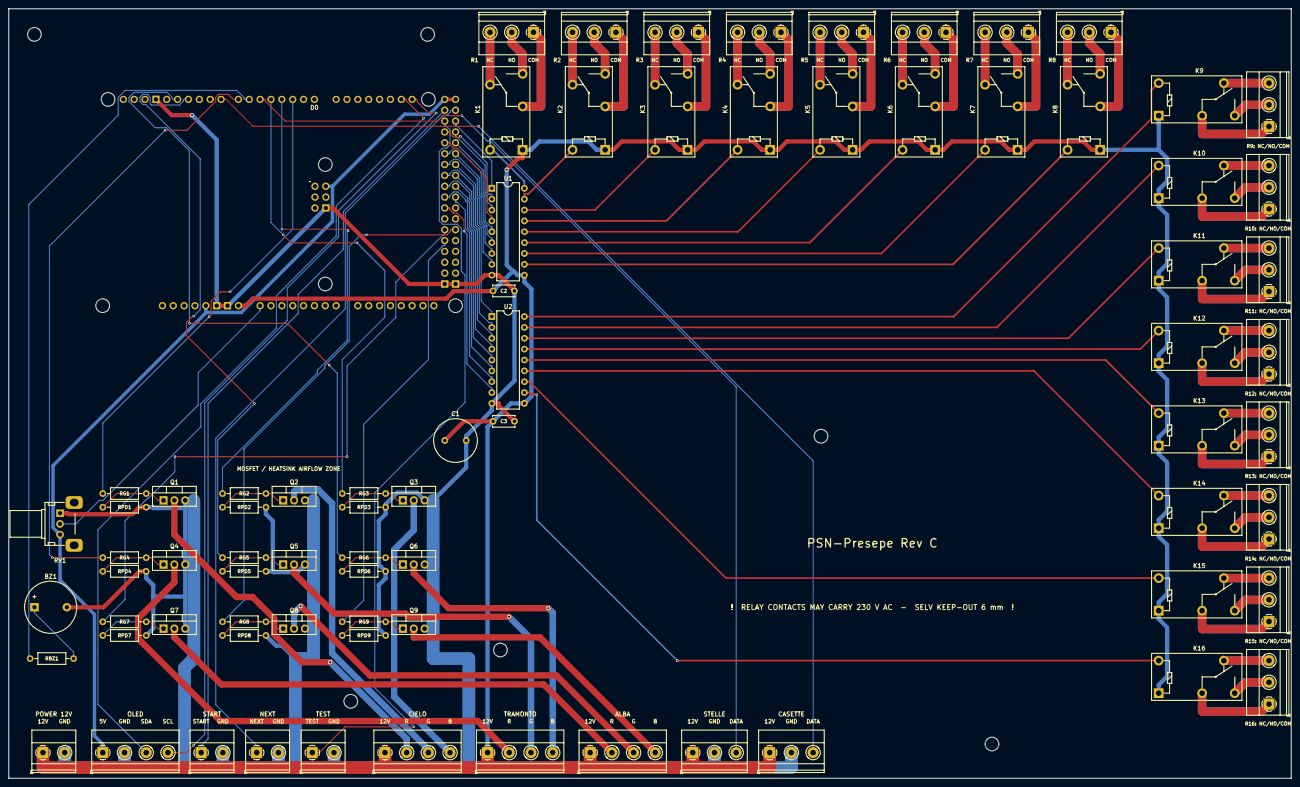
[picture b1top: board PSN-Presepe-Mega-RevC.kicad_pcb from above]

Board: 2 copper layers, 300.0 x 180.0 mm, 84 parts (0 on the bottom side), 120 nets.

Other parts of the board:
H1, H2, H3, H4, H5, H6: M3_NPTH; MountingHole_3.2mm_M3
